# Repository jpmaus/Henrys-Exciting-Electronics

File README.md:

# Henrys-Exciting-Electronics
EAGLE PCB Designs for Various Schematics From [interestingelectronics.com.](https://www.interestingelectronics.com)
With Eurorack Power Headers.  
Note: stackable pot/jack faceplate PCBs are missing.  Please look at Henry's schematics, design the stackable pot/jack boards in EAGLE CAD, let me know, and I'll merge them...  If I ever get the time to print them myself, then I'll upload them, but I'm so short on time these days!

FOR SALE, I had a small run of 5 each done for the Dual Analogue Frequency Shifter and the Ithycoo Tape Flanger, you can purchase them here, if you buy one and design a pot & jack board be sure and share it with me! [BUY PCBS](https://demonstration-bootleg.com/shop/ols/categories/pcb)

## Ambisonic "Clock Outputs" Decoder with Special Crosstalk Cancellation
[Ambisonic "Clock Outputs" Decoder with Special Crosstalk Cancellation](https://www.interestingelectronics.com/old/henrys_interesting_electronics/ambisonic_decoder/ambisonic_clock_decoder/ambisonic_clock_decoder.htm)

## Dual Analogue Frequency Shifter
[Dual Analogue Frequency Shifter](https://www.interestingelectronics.com/old/henrys_interesting_electronics/frequency_shifter/frequency_shifter.htm)

## Itchycoo Tape Flanger  
[Itchycoo Tape Flanger](https://www.interestingelectronics.com/old/henrys_interesting_electronics/flanger/flanger.htm)

## Oscillator Or Joystick Ambisonic Pan-Rotate
[Oscillator Or Joystick Ambisonic Pan-Rotate](https://www.interestingelectronics.com/old/henrys_interesting_electronics/ambisonic_swinger/ambisonic_swinger.htm)

## UHJ And B Format Ambisonic Decoder
[UHJ And B Format Ambisonic Decoder](https://www.interestingelectronics.com/old/henrys_interesting_electronics/ambisonic_decoder/ambisonic_decoder.htm)

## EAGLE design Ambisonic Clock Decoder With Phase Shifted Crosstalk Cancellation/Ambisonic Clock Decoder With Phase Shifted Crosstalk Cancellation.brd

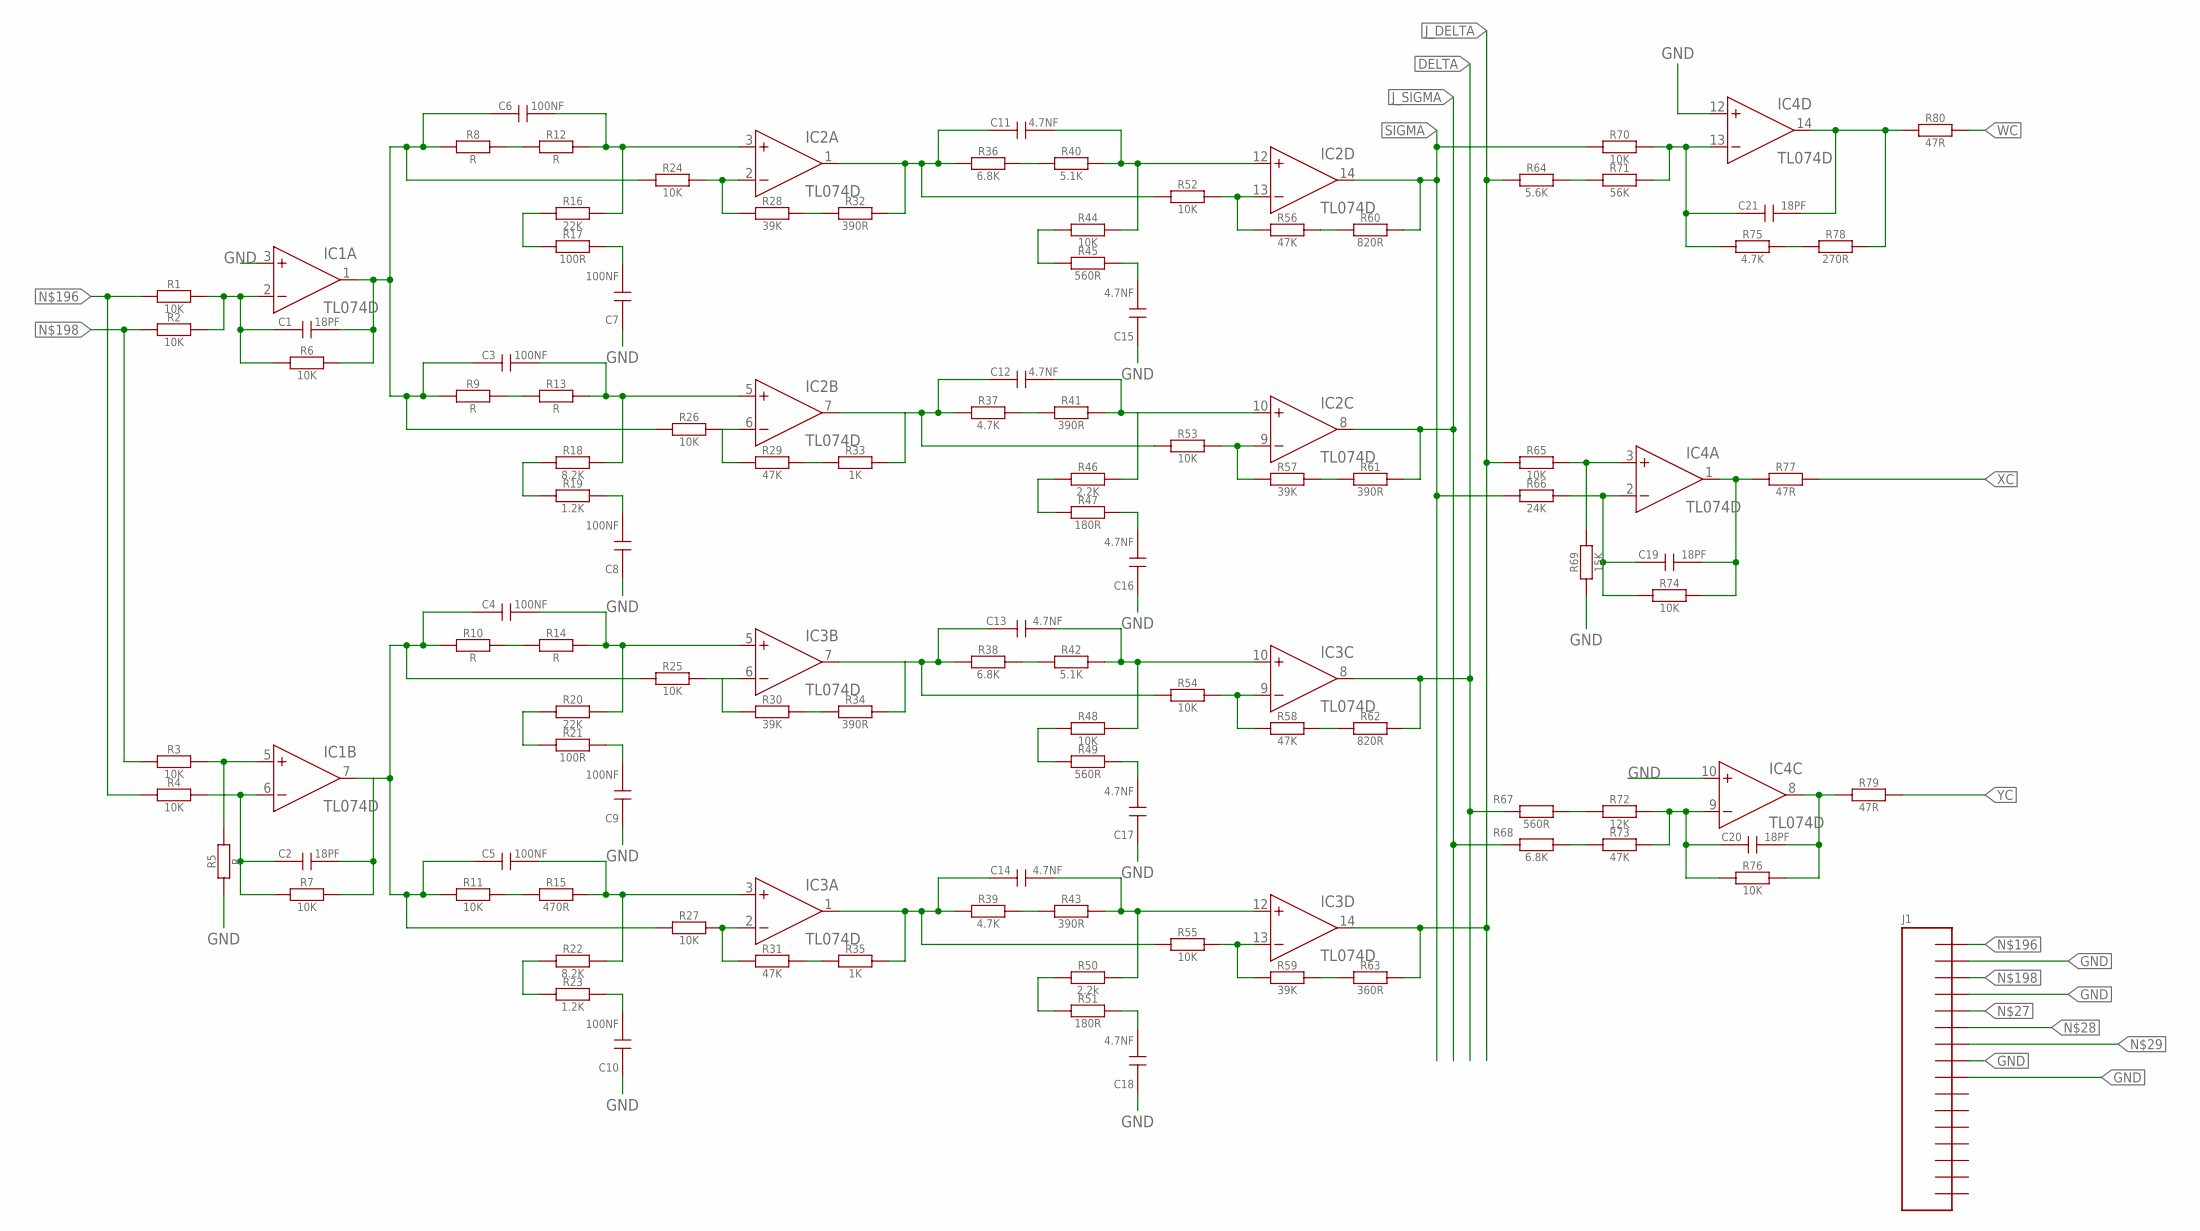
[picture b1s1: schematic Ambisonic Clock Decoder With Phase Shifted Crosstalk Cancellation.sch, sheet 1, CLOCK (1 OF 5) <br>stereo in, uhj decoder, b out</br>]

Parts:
C1, C2, C19, C20, C21: 18PF; CT6032
C3, C4, C5, C6, C7, C8, C9, C10: 100NF; CT6032
C11, C12, C13, C14, C15, C16, C17, C18: 4.7NF; CT6032
IC1, IC2, IC3, IC4: TL074D; SO14
J1: CON_16; 2X08SMT
R1, R2, R3, R4, R6, R7, R11, R24, R25, R26, R27, R44, R48, R52, R53, R54, R55, R65, R70, R74, R76: 10K; R6332W
R5, R8, R9, R10, R12, R13, R14: R; R6332W
R15: 470R; R6332W
R16, R20: 22K; R6332W
R17, R21: 100R; R6332W
R18, R22: 8.2K; R6332W
R19, R23: 1.2K; R6332W
R28, R30, R57, R59: 39K; R6332W
R29, R31, R56, R58, R73: 47K; R6332W
R32, R34, R41, R43, R61: 390R; R6332W
R33, R35: 1K; R6332W
R36, R38, R68: 6.8K; R6332W
R37, R39, R75: 4.7K; R6332W
R40, R42: 5.1K; R6332W
R45, R49, R67: 560R; R6332W
R46: 2.2K; R6332W
R47, R51: 180R; R6332W
R50: 2.2k; R6332W
R60, R62: 820R; R6332W
R63: 360R; R6332W
R64: 5.6K; R6332W
R66: 24K; R6332W
R69: 15K; R6332W
R71: 56K; R6332W
R72: 12K; R6332W
R77, R79, R80: 47R; R6332W
R78: 270R; R6332W

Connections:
DELTA: IC3.8 (OUT), R62.2, R67.1
GND: C7.+ (1), C8.+ (1), C9.+ (1), C10.+ (1), C15.+ (1), C16.+ (1), C17.+ (1), C18.+ (1), IC1.3 (+IN), IC4.10 (+IN), IC4.12 (+IN), J1.2, J1.4, J1.8, J1.9, R5.1, R69.1; also elsewhere on the board
J_DELTA: IC3.14 (OUT), R63.2, R64.1, R65.1
J_SIGMA: IC2.8 (OUT), R61.2, R68.1
unnamed: R67.2, R72.1
unnamed: R68.2, R73.1
unnamed: C3.- (2), IC2.5 (+IN), R13.2, R18.2
unnamed: R16.1, R17.1
unnamed: R8.2, R12.1
unnamed: C7.- (2), R17.2
unnamed: C1.+ (1), IC1.2 (-IN), R1.2, R2.2, R6.1
unnamed: C1.- (2), C3.+ (1), C6.+ (1), IC1.1 (OUT), R6.2, R8.1, R9.1, R24.1, R26.1
unnamed: C6.- (2), IC2.3 (+IN), R12.2, R16.2
unnamed: C2.+ (1), IC1.6 (-IN), R4.2, R7.1
unnamed: C19.+ (1), IC4.2 (-IN), R66.2, R74.1
unnamed: R28.2, R32.1
unnamed: IC2.2 (-IN), R24.2, R28.1
unnamed: R10.2, R14.1
unnamed: C11.+ (1), IC2.1 (OUT), R32.2, R36.1, R52.1
unnamed: J1.1, R1.1, R4.1
unnamed: R36.2, R40.1
unnamed: J1.3, R2.1, R3.1
unnamed: C11.- (2), IC2.12 (+IN), R40.2, R44.2
unnamed: IC1.5 (+IN), R3.2, R5.2
unnamed: R44.1, R45.1
unnamed: C15.- (2), R45.2
unnamed: IC2.13 (-IN), R52.2, R56.1
unnamed: R56.2, R60.1
unnamed: R9.2, R13.1
unnamed: R18.1, R19.1
unnamed: C8.- (2), R19.2
unnamed: IC2.6 (-IN), R26.2, R29.1
unnamed: R29.2, R33.1
unnamed: C12.+ (1), IC2.7 (OUT), R33.2, R37.1, R53.1
unnamed: R37.2, R41.1
unnamed: C12.- (2), IC2.10 (+IN), R41.2, R46.2
unnamed: R46.1, R47.1
unnamed: C16.- (2), R47.2
unnamed: IC2.9 (-IN), R53.2, R57.1
unnamed: R57.2, R61.1
unnamed: C4.- (2), IC3.5 (+IN), R14.2, R20.2
unnamed: R20.1, R21.1
unnamed: C9.- (2), R21.2
unnamed: IC3.6 (-IN), R25.2, R30.1
unnamed: R30.2, R34.1
unnamed: C13.+ (1), IC3.7 (OUT), R34.2, R38.1, R54.1
unnamed: R38.2, R42.1
unnamed: C13.- (2), IC3.10 (+IN), R42.2, R48.2
unnamed: R48.1, R49.1
unnamed: C17.- (2), R49.2
unnamed: IC3.9 (-IN), R54.2, R58.1
unnamed: R58.2, R62.1
unnamed: R11.2, R15.1
unnamed: C5.- (2), IC3.3 (+IN), R15.2, R22.2
unnamed: R22.1, R23.1
unnamed: C10.- (2), R23.2
unnamed: IC3.2 (-IN), R27.2, R31.1
unnamed: R31.2, R35.1
unnamed: C14.+ (1), IC3.1 (OUT), R35.2, R39.1, R55.1
unnamed: R39.2, R43.1
unnamed: C14.- (2), IC3.12 (+IN), R43.2, R50.2
unnamed: R50.1, R51.1
unnamed: C18.- (2), R51.2
unnamed: IC3.13 (-IN), R55.2, R59.1
unnamed: R59.2, R63.1
unnamed: C2.- (2), C4.+ (1), C5.+ (1), IC1.7 (OUT), R7.2, R10.1, R11.1, R25.1, R27.1
unnamed: R64.2, R71.1
unnamed: IC4.3 (+IN), R65.2, R69.2
unnamed: C19.- (2), IC4.1 (OUT), R74.2, R77.1
unnamed: C21.+ (1), IC4.13 (-IN), R70.2, R71.2, R75.1
unnamed: R75.2, R78.1
unnamed: C21.- (2), IC4.14 (OUT), R78.2, R80.1
unnamed: C20.+ (1), IC4.9 (-IN), R72.2, R73.2, R76.1
unnamed: C20.- (2), IC4.8 (OUT), R76.2, R79.1
SIGMA: IC2.14 (OUT), R60.2, R66.1, R70.1
V+: IC1.4 (V+), IC2.4 (V+), IC3.4 (V+), IC4.4 (V+); also elsewhere on the board
V-: IC1.11 (V-), IC2.11 (V-), IC3.11 (V-), IC4.11 (V-); also elsewhere on the board
WC: R80.2; also elsewhere on the board
XC: R77.2; also elsewhere on the board
YC: R79.2; also elsewhere on the board

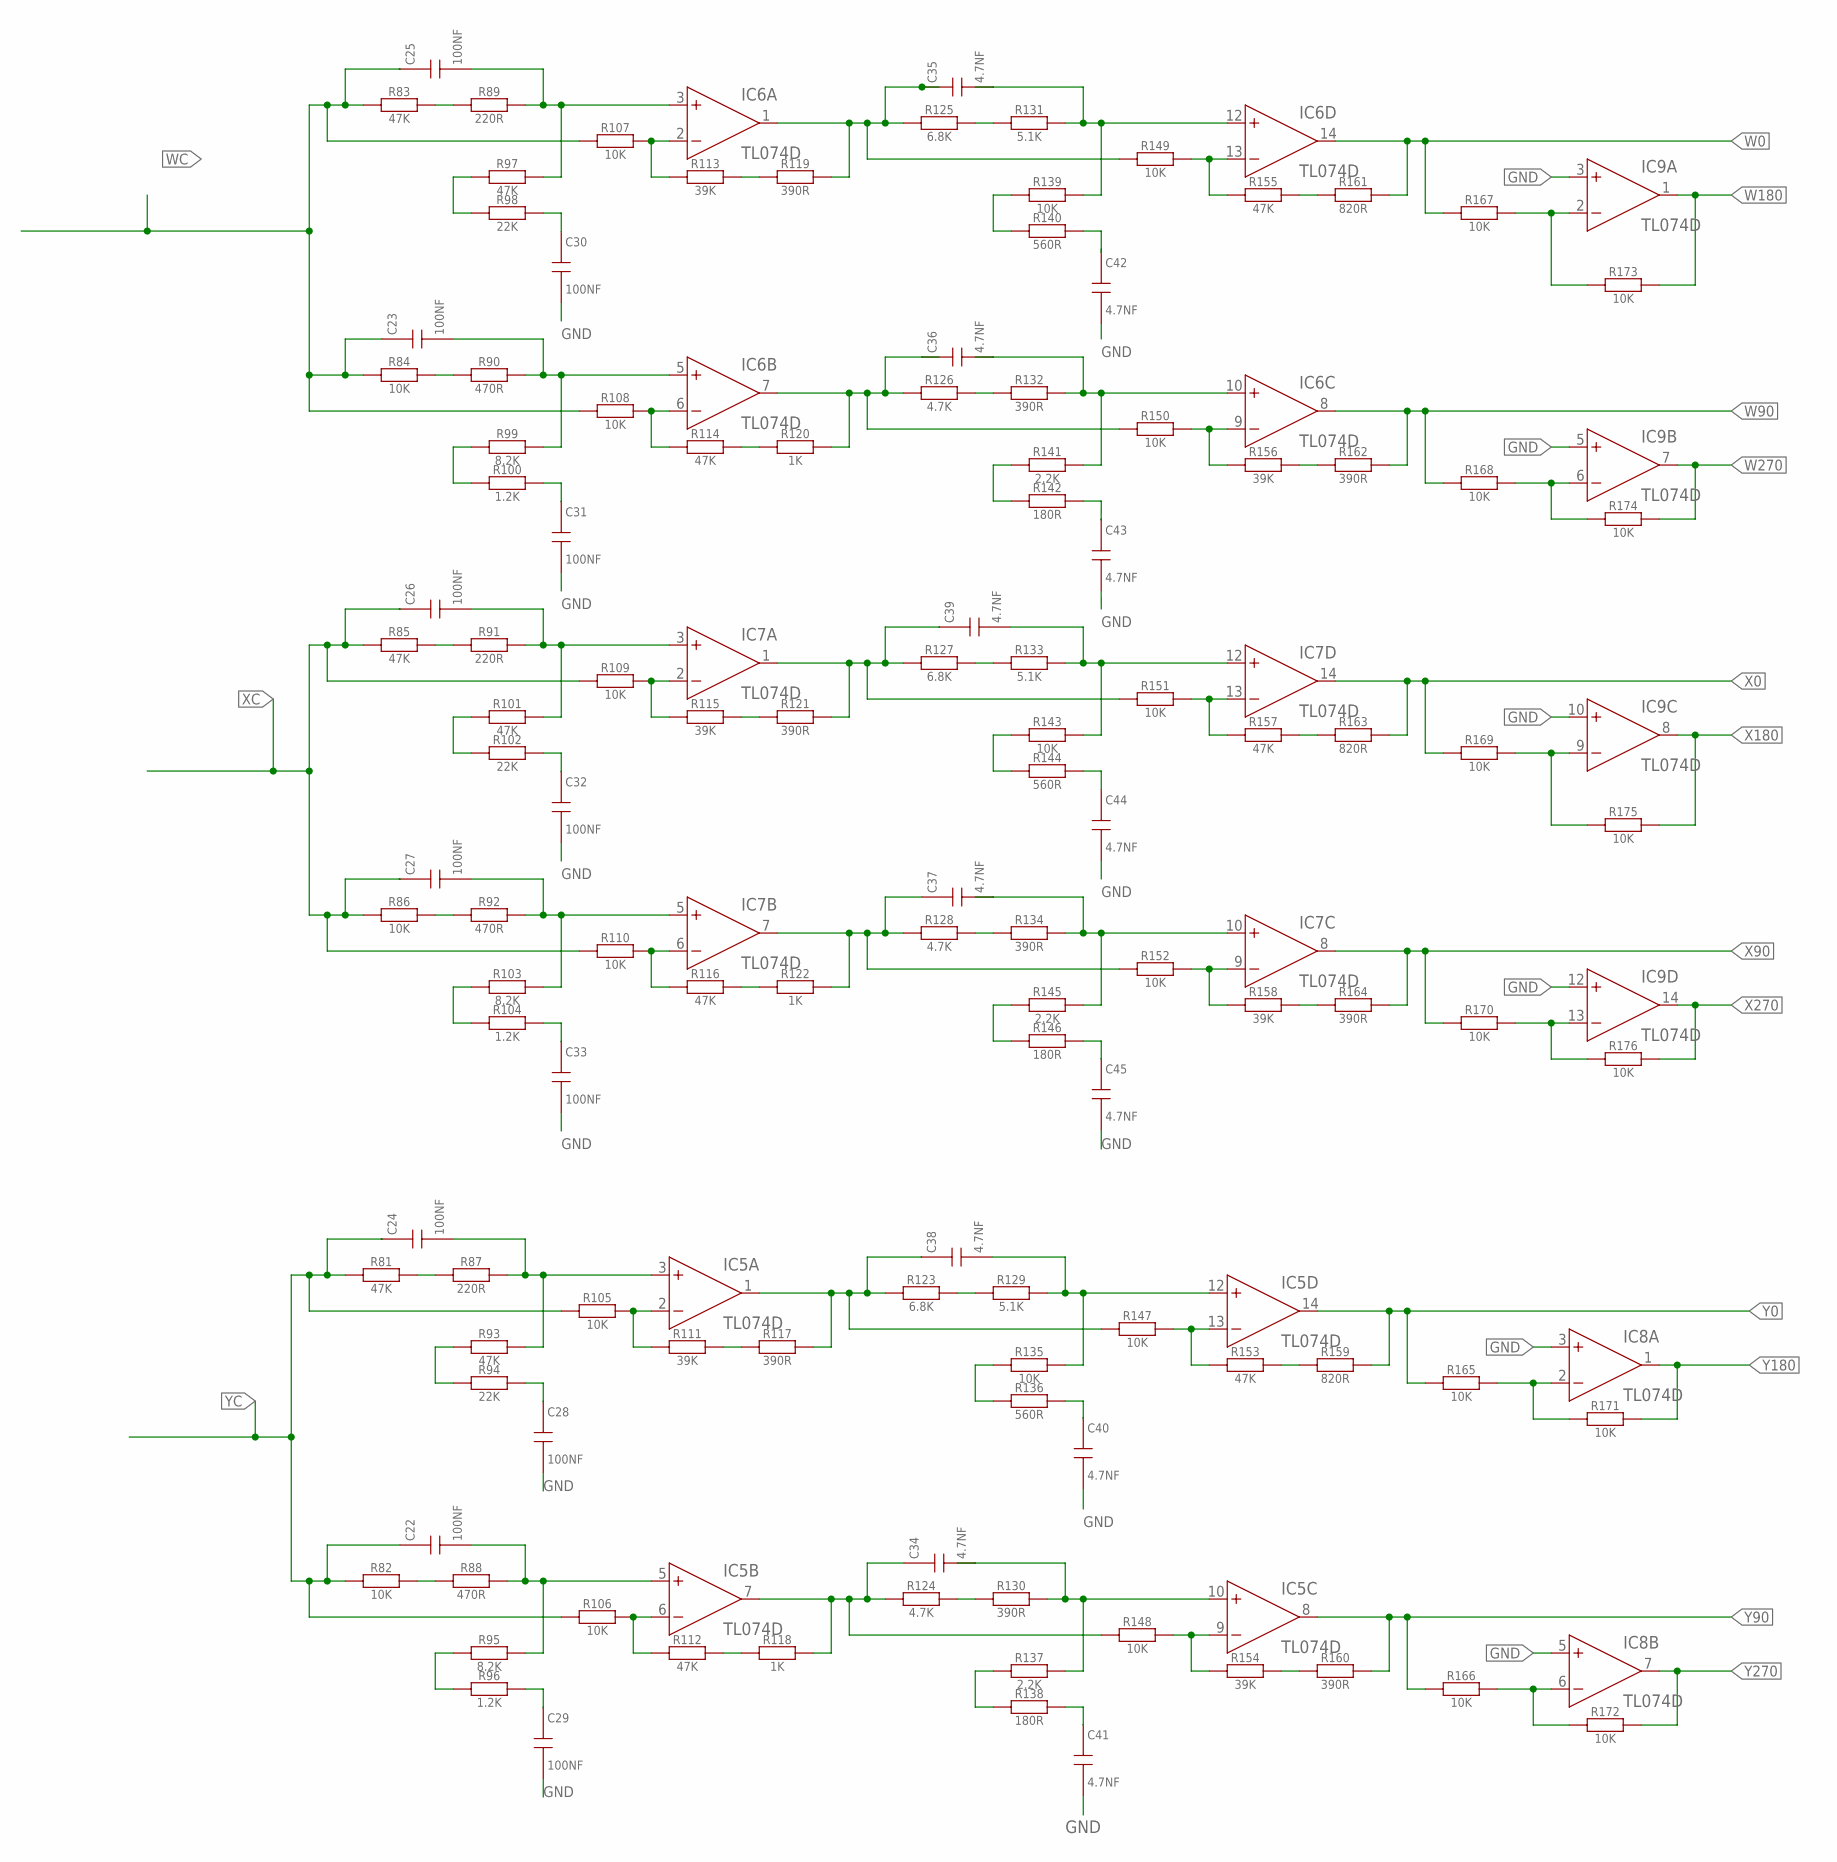
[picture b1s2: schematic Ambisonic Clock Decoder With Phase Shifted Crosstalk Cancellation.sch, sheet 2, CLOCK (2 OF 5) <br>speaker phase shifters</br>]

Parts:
C22, C23, C24, C25, C26, C27, C28, C29, C30, C31, C32, C33: 100NF; CT6032
C34, C35, C36, C37, C38, C39, C40, C41, C42, C43, C44, C45: 4.7NF; CT6032
IC5, IC6, IC7, IC8, IC9: TL074D; SO14
R81, R83, R85, R93, R97, R101, R112, R114, R116, R153, R155, R157: 47K; R6332W
R82, R84, R86, R105, R106, R107, R108, R109, R110, R135, R139, R143, R147, R148, R149, R150, R151, R152, R165, R166, R167, R168, R169, R170, R171, R172, R173, R174, R175, R176: 10K; R6332W
R87, R89, R91: 220R; R6332W
R88, R90, R92: 470R; R6332W
R94, R98, R102: 22K; R6332W
R95, R99, R103: 8.2K; R6332W
R96, R100, R104: 1.2K; R6332W
R111, R113, R115, R154, R156, R158: 39K; R6332W
R117, R119, R121, R130, R132, R134, R160, R162, R164: 390R; R6332W
R118, R120, R122: 1K; R6332W
R123, R125, R127: 6.8K; R6332W
R124, R126, R128: 4.7K; R6332W
R129, R131, R133: 5.1K; R6332W
R136, R140, R144: 560R; R6332W
R137, R141, R145: 2.2K; R6332W
R138, R142, R146: 180R; R6332W
R159, R161, R163: 820R; R6332W

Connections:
GND: C28.- (2), C29.- (2), C30.- (2), C31.- (2), C32.- (2), C33.- (2), C40.- (2), C41.- (2), C42.- (2), C43.- (2), C44.- (2), C45.- (2), IC8.3 (+IN), IC8.5 (+IN), IC9.3 (+IN), IC9.5 (+IN), IC9.10 (+IN), IC9.12 (+IN); also elsewhere on the board
unnamed: R82.2, R88.1
unnamed: R95.1, R96.1
unnamed: C29.+ (1), R96.2
unnamed: IC5.6 (-IN), R106.2, R112.1
unnamed: R112.2, R118.1
unnamed: C34.+ (1), IC5.7 (OUT), R118.2, R124.1, R148.1
unnamed: R124.2, R130.1
unnamed: R137.1, R138.1
unnamed: C41.+ (1), R138.2
unnamed: IC5.9 (-IN), R148.2, R154.1
unnamed: R154.2, R160.1
unnamed: R81.2, R87.1
unnamed: R93.1, R94.1
unnamed: C28.+ (1), R94.2
unnamed: IC5.2 (-IN), R105.2, R111.1
unnamed: R111.2, R117.1
unnamed: C38.+ (1), IC5.1 (OUT), R117.2, R123.1, R147.1
unnamed: R123.2, R129.1
unnamed: R135.1, R136.1
unnamed: C40.+ (1), R136.2
unnamed: IC5.13 (-IN), R147.2, R153.1
unnamed: R153.2, R159.1
unnamed: R84.2, R90.1
unnamed: R99.1, R100.1
unnamed: C31.+ (1), R100.2
unnamed: IC6.6 (-IN), R108.2, R114.1
unnamed: R114.2, R120.1
unnamed: C36.+ (1), IC6.7 (OUT), R120.2, R126.1, R150.1
unnamed: R126.2, R132.1
unnamed: R141.1, R142.1
unnamed: C43.+ (1), R142.2
unnamed: IC6.9 (-IN), R150.2, R156.1
unnamed: R156.2, R162.1
unnamed: R83.2, R89.1
unnamed: R97.1, R98.1
unnamed: IC8.6 (-IN), R166.2, R172.1
unnamed: C30.+ (1), R98.2
unnamed: IC6.2 (-IN), R107.2, R113.1
unnamed: R113.2, R119.1
unnamed: C35.+ (1), IC6.1 (OUT), R119.2, R125.1, R149.1
unnamed: R125.2, R131.1
unnamed: R139.1, R140.1
unnamed: C42.+ (1), R140.2
unnamed: IC6.13 (-IN), R149.2, R155.1
unnamed: R155.2, R161.1
unnamed: IC8.2 (-IN), R165.2, R171.1
unnamed: R86.2, R92.1
unnamed: C27.- (2), IC7.5 (+IN), R92.2, R103.2
unnamed: R103.1, R104.1
unnamed: C33.+ (1), R104.2
unnamed: IC7.6 (-IN), R110.2, R116.1
unnamed: R116.2, R122.1
unnamed: C37.+ (1), IC7.7 (OUT), R122.2, R128.1, R152.1
unnamed: R128.2, R134.1
unnamed: R145.1, R146.1
unnamed: C45.+ (1), R146.2
unnamed: IC7.9 (-IN), R152.2, R158.1
unnamed: R158.2, R164.1
unnamed: IC9.13 (-IN), R170.2, R176.1
unnamed: R85.2, R91.1
unnamed: R101.1, R102.1
unnamed: C32.+ (1), R102.2
unnamed: IC7.2 (-IN), R109.2, R115.1
unnamed: R115.2, R121.1
unnamed: C39.+ (1), IC7.1 (OUT), R121.2, R127.1, R151.1
unnamed: R127.2, R133.1
unnamed: R143.1, R144.1
unnamed: C44.+ (1), R144.2
unnamed: IC7.13 (-IN), R151.2, R157.1
unnamed: R157.2, R163.1
unnamed: IC9.9 (-IN), R169.2, R175.1
unnamed: IC9.6 (-IN), R168.2, R174.1
unnamed: IC9.2 (-IN), R167.2, R173.1
unnamed: C26.- (2), IC7.3 (+IN), R91.2, R101.2
unnamed: C22.- (2), IC5.5 (+IN), R88.2, R95.2
unnamed: C24.- (2), IC5.3 (+IN), R87.2, R93.2
unnamed: C23.- (2), IC6.5 (+IN), R90.2, R99.2
unnamed: C25.- (2), IC6.3 (+IN), R89.2, R97.2
unnamed: C35.- (2), IC6.12 (+IN), R131.2, R139.2
unnamed: C36.- (2), IC6.10 (+IN), R132.2, R141.2
unnamed: C38.- (2), IC5.12 (+IN), R129.2, R135.2
unnamed: C34.- (2), IC5.10 (+IN), R130.2, R137.2
unnamed: C37.- (2), IC7.10 (+IN), R134.2, R145.2
unnamed: C39.- (2), IC7.12 (+IN), R133.2, R143.2
V+: IC5.4 (V+), IC6.4 (V+), IC7.4 (V+), IC8.4 (V+), IC9.4 (V+); also elsewhere on the board
V-: IC5.11 (V-), IC6.11 (V-), IC7.11 (V-), IC8.11 (V-), IC9.11 (V-); also elsewhere on the board
W0: IC6.14 (OUT), R161.2, R167.1; also elsewhere on the board
W90: IC6.8 (OUT), R162.2, R168.1; also elsewhere on the board
W180: IC9.1 (OUT), R173.2; also elsewhere on the board
W270: IC9.7 (OUT), R174.2; also elsewhere on the board
WC: C23.+ (1), C25.+ (1), R83.1, R84.1, R107.1, R108.1; also elsewhere on the board
X0: IC7.14 (OUT), R163.2, R169.1; also elsewhere on the board
X90: IC7.8 (OUT), R164.2, R170.1; also elsewhere on the board
X180: IC9.8 (OUT), R175.2
X270: IC9.14 (OUT), R176.2; also elsewhere on the board
XC: C26.+ (1), C27.+ (1), R85.1, R86.1, R109.1, R110.1; also elsewhere on the board
Y0: IC5.14 (OUT), R159.2, R165.1; also elsewhere on the board
Y90: IC5.8 (OUT), R160.2, R166.1; also elsewhere on the board
Y180: IC8.1 (OUT), R171.2; also elsewhere on the board
Y270: IC8.7 (OUT), R172.2
YC: C22.+ (1), C24.+ (1), R81.1, R82.1, R105.1, R106.1; also elsewhere on the board

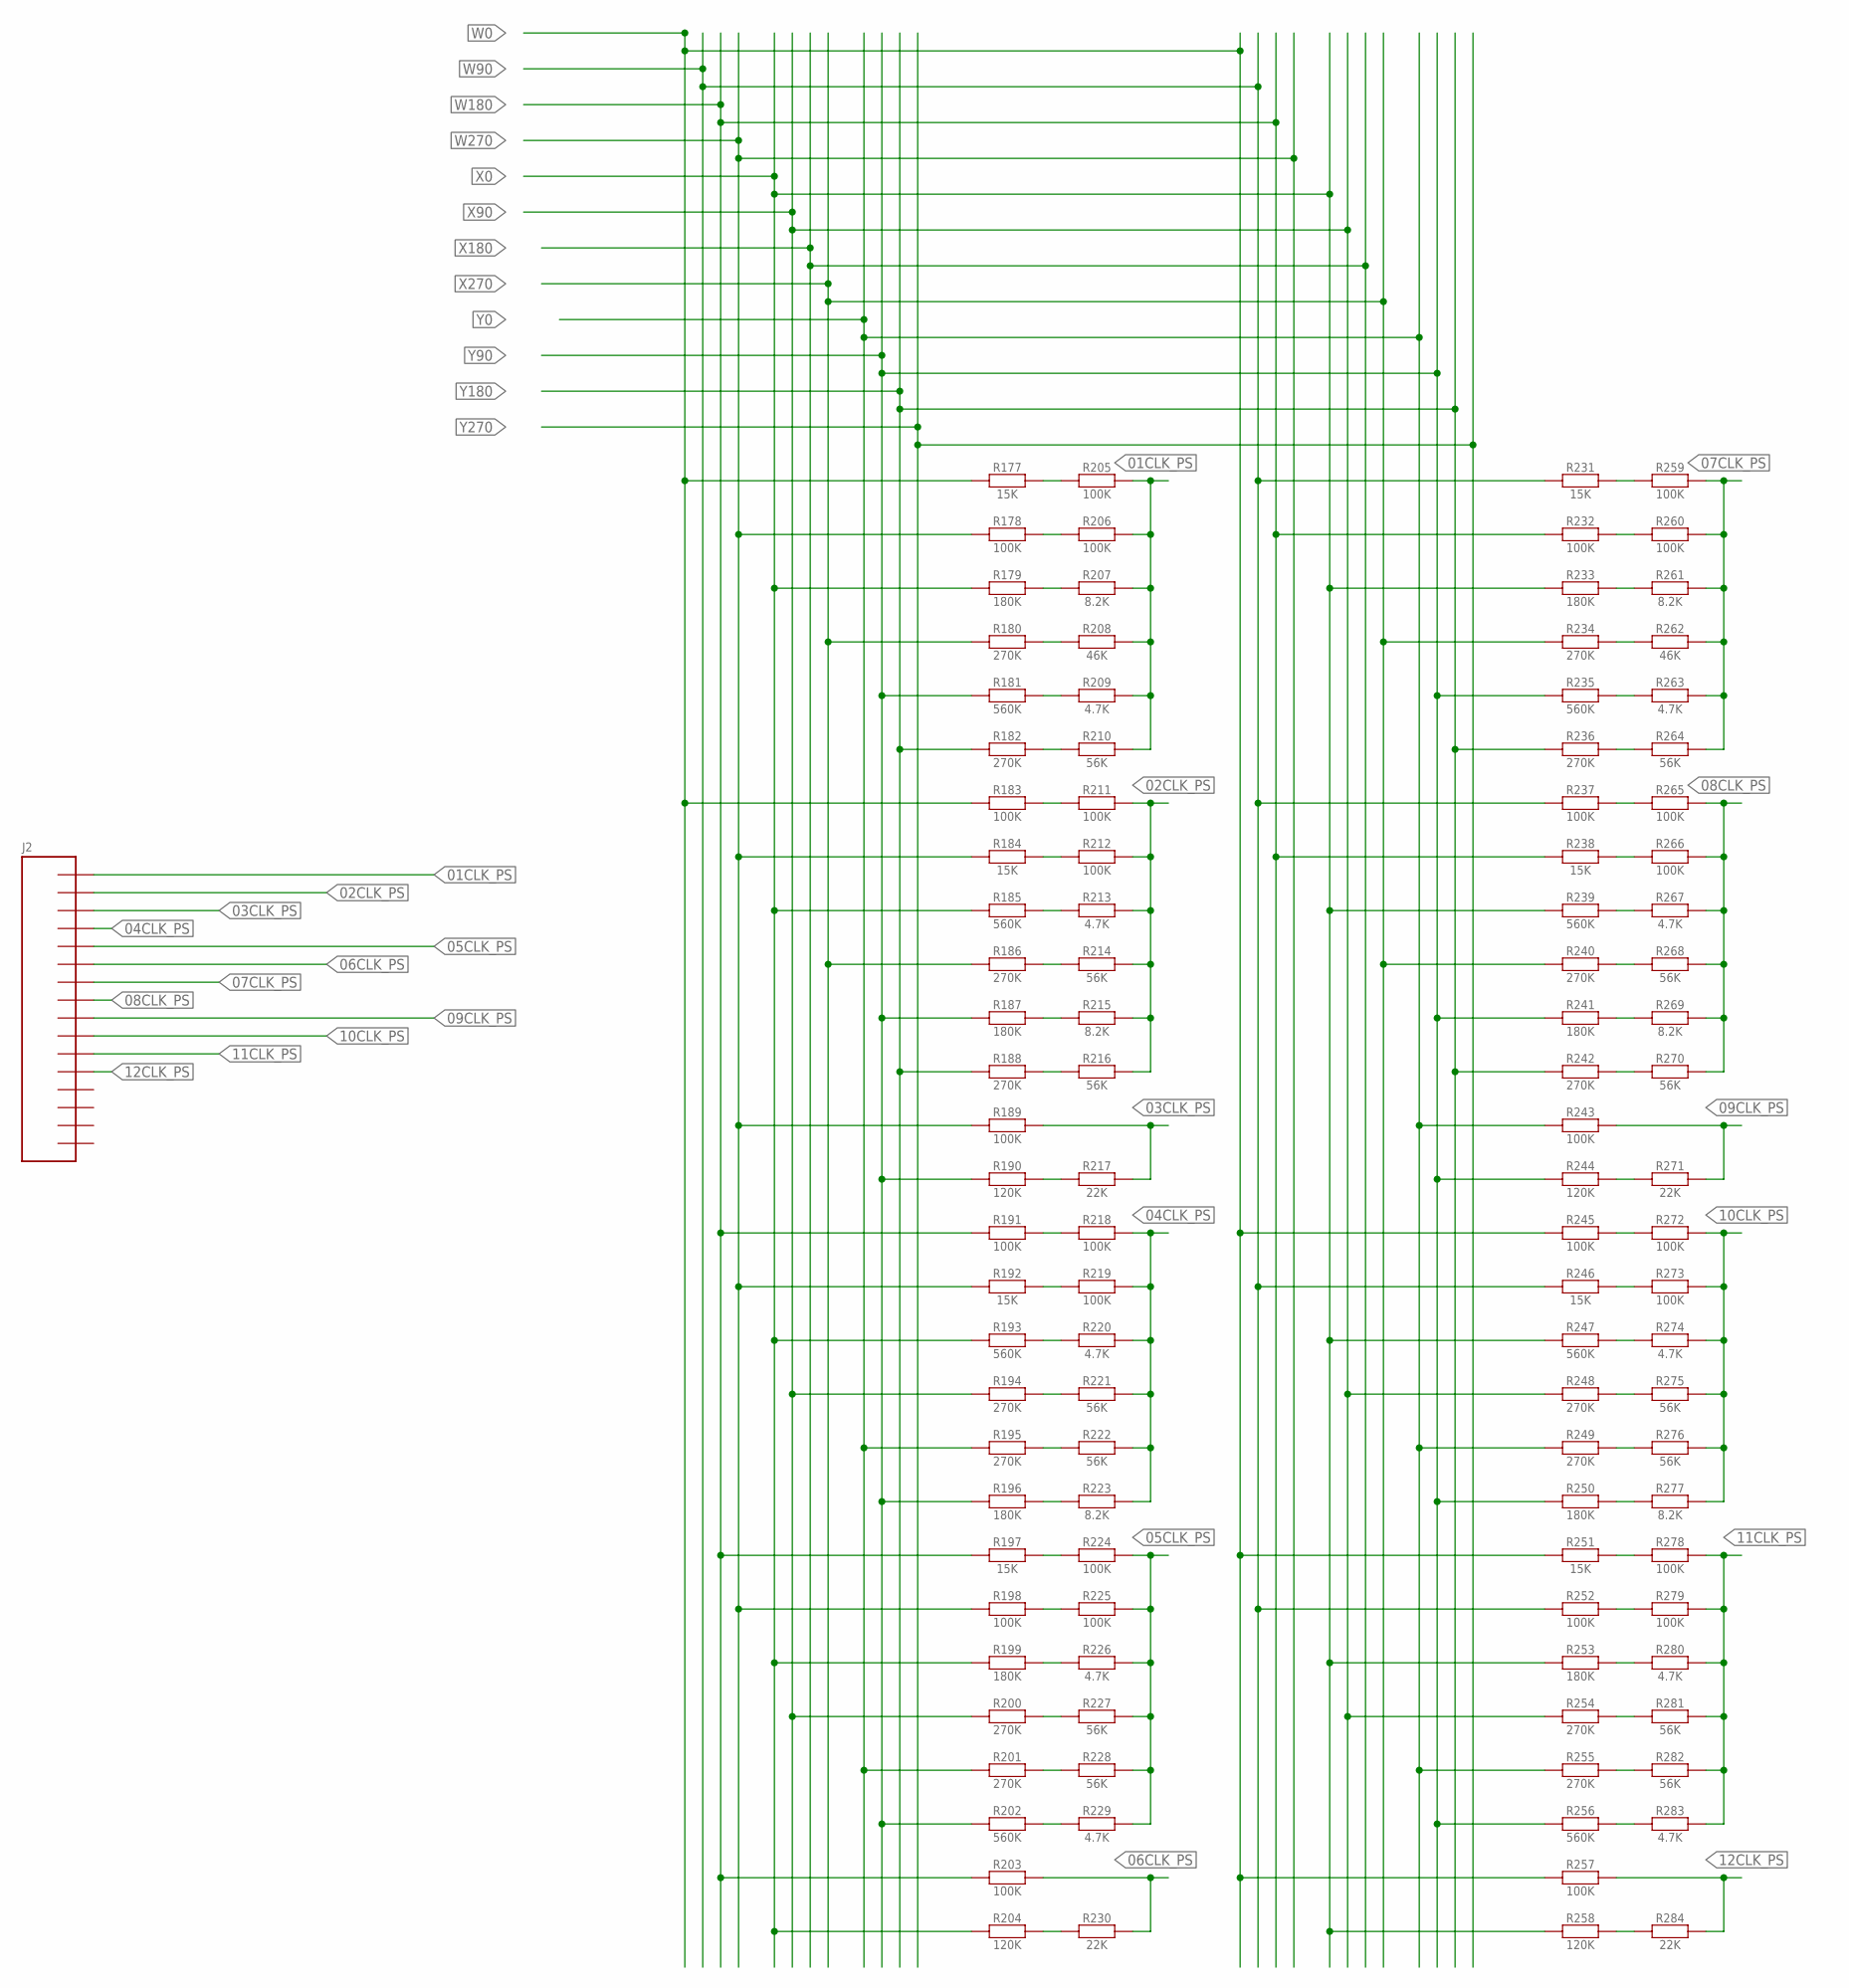
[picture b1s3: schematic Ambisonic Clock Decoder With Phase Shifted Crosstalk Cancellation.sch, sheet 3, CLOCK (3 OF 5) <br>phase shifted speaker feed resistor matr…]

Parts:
J2: CON_16; 2X08SMT
R177, R184, R192, R197, R231, R238, R246, R251: 15K; R6332W
R178, R183, R189, R191, R198, R203, R205, R206, R211, R212, R218, R219, R224, R225, R232, R237, R243, R245, R252, R257, R259, R260, R265, R266, R272, R273, R278, R279: 100K; R6332W
R179, R187, R196, R199, R233, R241, R250, R253: 180K; R6332W
R180, R182, R186, R188, R194, R195, R200, R201, R234, R236, R240, R242, R248, R249, R254, R255: 270K; R6332W
R181, R185, R193, R202, R235, R239, R247, R256: 560K; R6332W
R190, R204, R244, R258: 120K; R6332W
R207, R215, R223, R261, R269, R277: 8.2K; R6332W
R208, R262: 46K; R6332W
R209, R213, R220, R226, R229, R263, R267, R274, R280, R283: 4.7K; R6332W
R210, R214, R216, R221, R222, R227, R228, R264, R268, R270, R275, R276, R281, R282: 56K; R6332W
R217, R230, R271, R284: 22K; R6332W

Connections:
01CLK_PS: J2.1, R205.2, R206.2, R207.2, R208.2, R209.2, R210.2
02CLK_PS: J2.2, R211.2, R212.2, R213.2, R214.2, R215.2, R216.2
03CLK_PS: J2.3, R189.2, R217.2
04CLK_PS: J2.4, R218.2, R219.2, R220.2, R221.2, R222.2, R223.2
05CLK_PS: J2.5, R224.2, R225.2, R226.2, R227.2, R228.2, R229.2
06CLK_PS: J2.6, R203.2, R230.2
07CLK_PS: J2.7, R259.2, R260.2, R261.2, R262.2, R263.2, R264.2
08CLK_PS: J2.8, R265.2, R266.2, R267.2, R268.2, R269.2, R270.2
09CLK_PS: J2.9, R243.2, R271.2
10CLK_PS: J2.10, R272.2, R273.2, R274.2, R275.2, R276.2, R277.2
11CLK_PS: J2.11, R278.2, R279.2, R280.2, R281.2, R282.2, R283.2
12CLK_PS: J2.12, R257.2, R284.2
unnamed: R237.2, R265.1
unnamed: R238.2, R266.1
unnamed: R239.2, R267.1
unnamed: R240.2, R268.1
unnamed: R241.2, R269.1
unnamed: R242.2, R270.1
unnamed: R244.2, R271.1
unnamed: R231.2, R259.1
unnamed: R232.2, R260.1
unnamed: R233.2, R261.1
unnamed: R234.2, R262.1
unnamed: R235.2, R263.1
unnamed: R236.2, R264.1
unnamed: R251.2, R278.1
unnamed: R252.2, R279.1
unnamed: R253.2, R280.1
unnamed: R254.2, R281.1
unnamed: R255.2, R282.1
unnamed: R256.2, R283.1
unnamed: R258.2, R284.1
unnamed: R245.2, R272.1
unnamed: R246.2, R273.1
unnamed: R247.2, R274.1
unnamed: R248.2, R275.1
unnamed: R249.2, R276.1
unnamed: R250.2, R277.1
unnamed: R183.2, R211.1
unnamed: R184.2, R212.1
unnamed: R185.2, R213.1
unnamed: R186.2, R214.1
unnamed: R187.2, R215.1
unnamed: R188.2, R216.1
unnamed: R190.2, R217.1
unnamed: R177.2, R205.1
unnamed: R178.2, R206.1
unnamed: R179.2, R207.1
unnamed: R180.2, R208.1
unnamed: R181.2, R209.1
unnamed: R182.2, R210.1
unnamed: R197.2, R224.1
unnamed: R198.2, R225.1
unnamed: R199.2, R226.1
unnamed: R200.2, R227.1
unnamed: R201.2, R228.1
unnamed: R202.2, R229.1
unnamed: R204.2, R230.1
unnamed: R191.2, R218.1
unnamed: R192.2, R219.1
unnamed: R193.2, R220.1
unnamed: R194.2, R221.1
unnamed: R195.2, R222.1
unnamed: R196.2, R223.1
W0: R177.1, R183.1, R245.1, R251.1, R257.1; also elsewhere on the board
W90: R231.1, R237.1, R246.1, R252.1; also elsewhere on the board
W180: R191.1, R197.1, R203.1, R232.1, R238.1; also elsewhere on the board
W270: R178.1, R184.1, R189.1, R192.1, R198.1; also elsewhere on the board
X0: R179.1, R185.1, R193.1, R199.1, R204.1, R233.1, R239.1, R247.1, R253.1, R258.1; also elsewhere on the board
X90: R194.1, R200.1, R248.1, R254.1; also elsewhere on the board
X270: R180.1, R186.1, R234.1, R240.1; also elsewhere on the board
Y0: R195.1, R201.1, R243.1, R249.1, R255.1; also elsewhere on the board
Y90: R181.1, R187.1, R190.1, R196.1, R202.1, R235.1, R241.1, R244.1, R250.1, R256.1; also elsewhere on the board
Y180: R182.1, R188.1, R236.1, R242.1; also elsewhere on the board

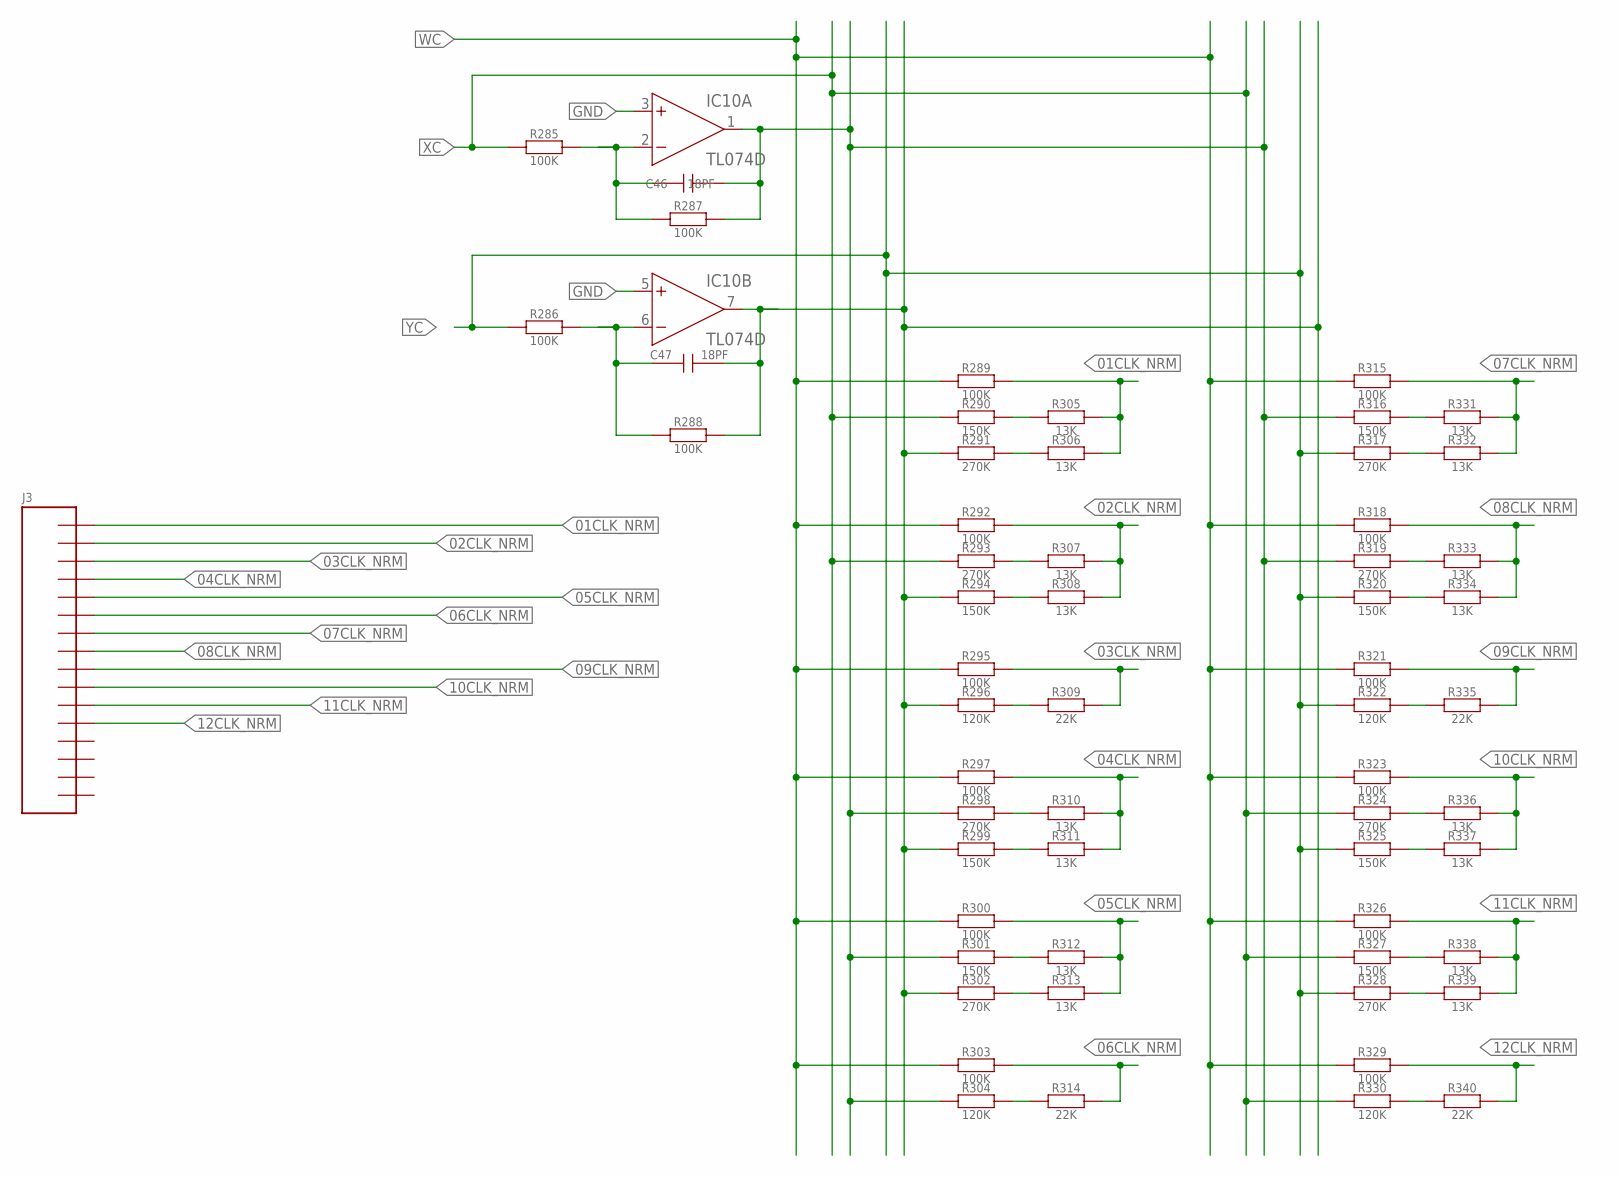
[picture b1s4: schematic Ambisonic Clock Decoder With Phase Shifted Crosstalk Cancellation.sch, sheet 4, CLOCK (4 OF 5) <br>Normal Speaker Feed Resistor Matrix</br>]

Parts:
C46, C47: 18PF; CT6032
IC10: TL074D; SO14
J3: CON_16; 2X08SMT
R285, R286, R287, R288, R289, R292, R295, R297, R300, R303, R315, R318, R321, R323, R326, R329: 100K; R6332W
R290, R294, R299, R301, R316, R320, R325, R327: 150K; R6332W
R291, R293, R298, R302, R317, R319, R324, R328: 270K; R6332W
R296, R304, R322, R330: 120K; R6332W
R305, R306, R307, R308, R310, R311, R312, R313, R331, R332, R333, R334, R336, R337, R338, R339: 13K; R6332W
R309, R314, R335, R340: 22K; R6332W

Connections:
01CLK_NRM: J3.1, R289.2, R305.2, R306.2
02CLK_NRM: J3.2, R292.2, R307.2, R308.2
03CLK_NRM: J3.3, R295.2, R309.2
04CLK_NRM: J3.4, R297.2, R310.2, R311.2
05CLK_NRM: J3.5, R300.2, R312.2, R313.2
06CLK_NRM: J3.6, R303.2, R314.2
07CLK_NRM: J3.7, R315.2, R331.2, R332.2
08CLK_NRM: J3.8, R318.2, R333.2, R334.2
09CLK_NRM: J3.9, R321.2, R335.2
10CLK_NRM: J3.10, R323.2, R336.2, R337.2
11CLK_NRM: J3.11, R326.2, R338.2, R339.2
12CLK_NRM: J3.12, R329.2, R340.2
GND: IC10.3 (+IN), IC10.5 (+IN); also elsewhere on the board
unnamed: C46.+ (1), IC10.2 (-IN), R285.2, R287.1
unnamed: C47.+ (1), IC10.6 (-IN), R286.2, R288.1
unnamed: R316.2, R331.1
unnamed: R317.2, R332.1
unnamed: R319.2, R333.1
unnamed: R320.2, R334.1
unnamed: R322.2, R335.1
unnamed: R324.2, R336.1
unnamed: R325.2, R337.1
unnamed: R327.2, R338.1
unnamed: R328.2, R339.1
unnamed: R330.2, R340.1
unnamed: R291.2, R306.1
unnamed: R290.2, R305.1
unnamed: R293.2, R307.1
unnamed: R294.2, R308.1
unnamed: R296.2, R309.1
unnamed: R298.2, R310.1
unnamed: R299.2, R311.1
unnamed: C47.- (2), IC10.7 (OUT), R288.2, R291.1, R294.1, R296.1, R299.1, R302.1
unnamed: R301.2, R312.1
unnamed: R302.2, R313.1
unnamed: R304.2, R314.1
V+: IC10.4 (V+); also elsewhere on the board
V-: IC10.11 (V-); also elsewhere on the board
WC: R289.1, R292.1, R295.1, R297.1, R300.1, R303.1, R315.1, R318.1, R321.1, R323.1, R326.1, R329.1; also elsewhere on the board
X1: C46.- (2), IC10.1 (OUT), R287.2, R298.1, R301.1, R304.1, R316.1, R319.1
XC: R285.1, R290.1, R293.1, R324.1, R327.1, R330.1; also elsewhere on the board
YC: R286.1, R317.1, R320.1, R322.1, R325.1, R328.1; also elsewhere on the board
